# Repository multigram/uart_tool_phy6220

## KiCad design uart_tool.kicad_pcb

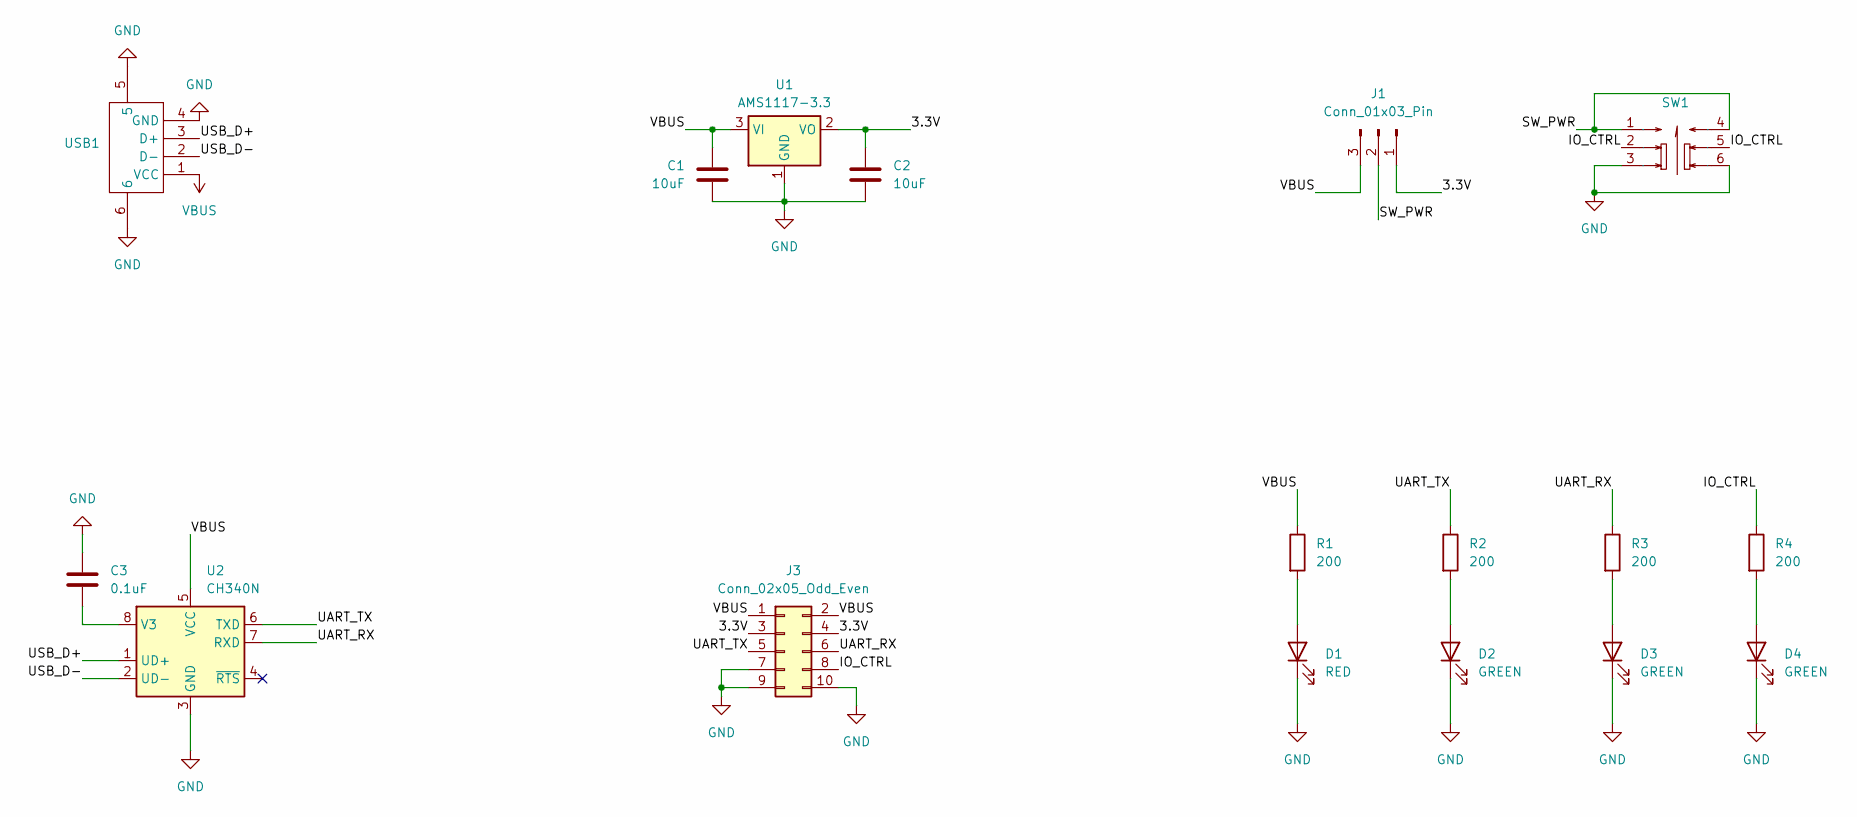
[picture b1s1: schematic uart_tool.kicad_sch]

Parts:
C1, C2: 10uF; C_0603_1608Metric_Pad1.08x0.95mm_HandSolder
C3: 0.1uF; C_0603_1608Metric_Pad1.08x0.95mm_HandSolder
D1: RED; D_0603_1608Metric_Pad1.05x0.95mm_HandSolder
D2, D3, D4: GREEN; D_0603_1608Metric_Pad1.05x0.95mm_HandSolder
J1: Conn_01x03_Pin; PinHeader_1x03_P2.54mm_Vertical
J3: Conn_02x05_Odd_Even; PinHeader_2x05_P2.54mm_Vertical
R1, R2, R3, R4: 200; R_0603_1608Metric_Pad0.98x0.95mm_HandSolder
SW1: SW-TH_6P-L7.0-W7.0-P2.00
U1: AMS1117-3.3; SOT-223-3_TabPin2
U2: CH340N; SOP-8_3.9x4.9mm_P1.27mm
USB1: USB-A-SMD_U217-041N-4BV81

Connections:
/3.3V: C2.1, J1.1, J3.3, J3.4, U1.2 (VO)
/IO_CTRL: J3.8, R4.1, SW1.2, SW1.5
/SW_PWR: J1.2, SW1.1, SW1.4
/UART_RX: J3.6, R3.1, U2.7 (RXD)
/UART_TX: J3.5, R2.1, U2.6 (TXD)
/USB_D+: U2.1 (UD+), USB1.3 (D+)
/USB_D-: U2.2 (UD-), USB1.2 (D-)
GND: C1.2, C2.2, C3.1, D1.1 (K), D2.1 (K), D3.1 (K), D4.1 (K), J3.7, J3.9, J3.10, SW1.3, SW1.6, U1.1 (GND), U2.3 (GND), USB1.4 (GND), USB1.5, USB1.6
unnamed: D1.2 (A), R1.2
unnamed: D2.2 (A), R2.2
unnamed: D3.2 (A), R3.2
unnamed: D4.2 (A), R4.2
unnamed: C3.2, U2.8 (V3)
VBUS: C1.1, J1.3, J3.1, J3.2, R1.1, U1.3 (VI), U2.5 (VCC), USB1.1 (VCC)

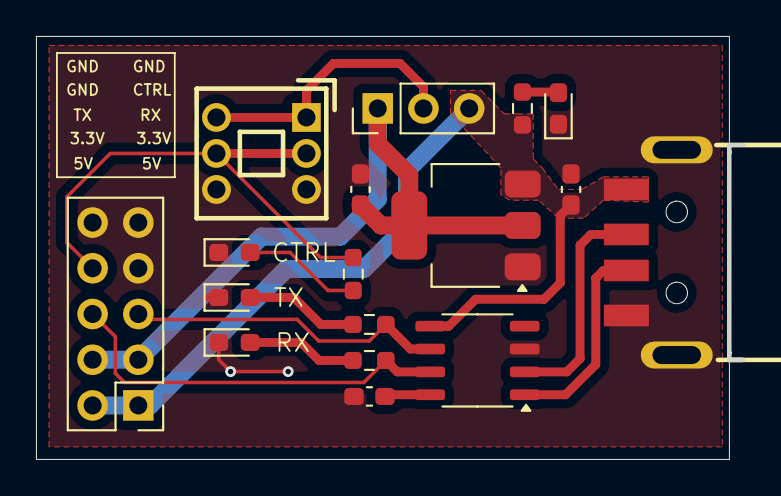
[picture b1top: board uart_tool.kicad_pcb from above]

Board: 2 copper layers, 39.2 x 23.3 mm, 17 parts (0 on the bottom side), 14 nets.
